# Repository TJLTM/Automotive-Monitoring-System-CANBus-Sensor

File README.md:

What is this? 
--- when working on my AMS solution i kept putting more and more stuff into a single box and everytime i needed to make a change it was $200 for a board that may or may not work so i decided to make it easier on myself to split the sensors up so that it isn't a bespoke solution for a single car application. 

these are the sensor hardware designs that match up with https://github.com/TJLTM/Automotive-Monitoring-System-CANBus-Sensor-FW repo so that i can keep the Hardware designs over here and the FW over there. mostly just so i'm not in some weird state where i'm working on a FW for one thing and the hardware for another and get into a screwed up merge situation. this has happened before in my other projects. 

If you look at the other repo you'll see i've made provisions for the following sensors 
* Temp (RTD)
* Voltage (ADC)
  * Pressure
  * Current
  * Temp (not RTD Based)
  * Any sensor that outputs a votlage signal if gain is needed that would have to be added
* Vacuum
* I/O
* RPM
* LED or other general Output
  * P-channel
  * N-channel  

The other boards ahve the hardware built on to the boards since those require some type of special sensor

Vacuum sensor 
This one is something that i've been working on for a while since there aren't many direct vacuum sensors out there and it took me a while to figure out this design as most vacuum sensors or MAPs so a bit of math to do it. They take the Barometric pressure and then making a few assumptions use the differential to standard atmospherical pressure to give you the vacuum. The design i am using is a direct measurement of the vacuum via the honeywell sensor. Yes it's expensive to build. In fact it costs more to make one of those then all the others combined. 

RPM sensor 
this one is a straight foreward design and i may make it an add on module for the ADC since really it's just a Freq to Voltage Sensor 

The I/O box... 
That one i'm making it a standard 8 in and 8 out setup. can be made to i don't know.... hook into power window units in older cars that can then be remotely controlled or in my case add power windows to some cars.

LED 
General 3 Channel RGB leds can be driven off of this I'm making it 4 channel since i have the space for it. It can either be high or low side switching depending on your application. this is using the 0-255 PWM output of the AVR

I'm using my other design for power https://github.com/TJLTM/LM2670SX-Carrier but if you don't like it. BYOPS

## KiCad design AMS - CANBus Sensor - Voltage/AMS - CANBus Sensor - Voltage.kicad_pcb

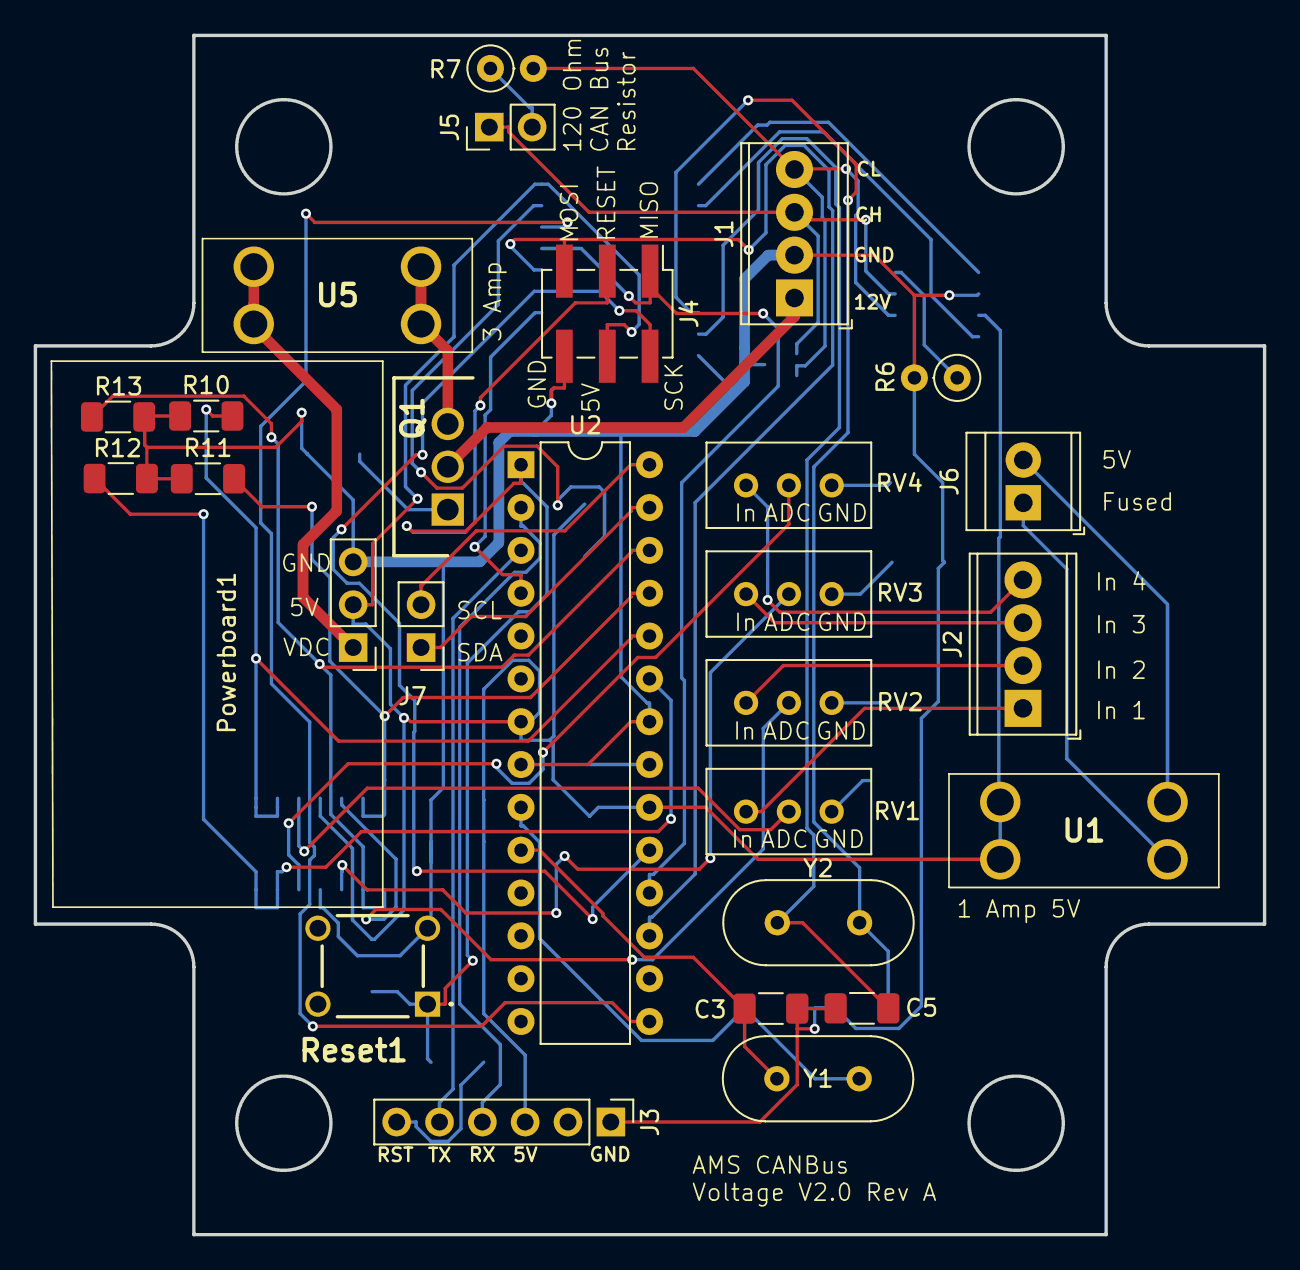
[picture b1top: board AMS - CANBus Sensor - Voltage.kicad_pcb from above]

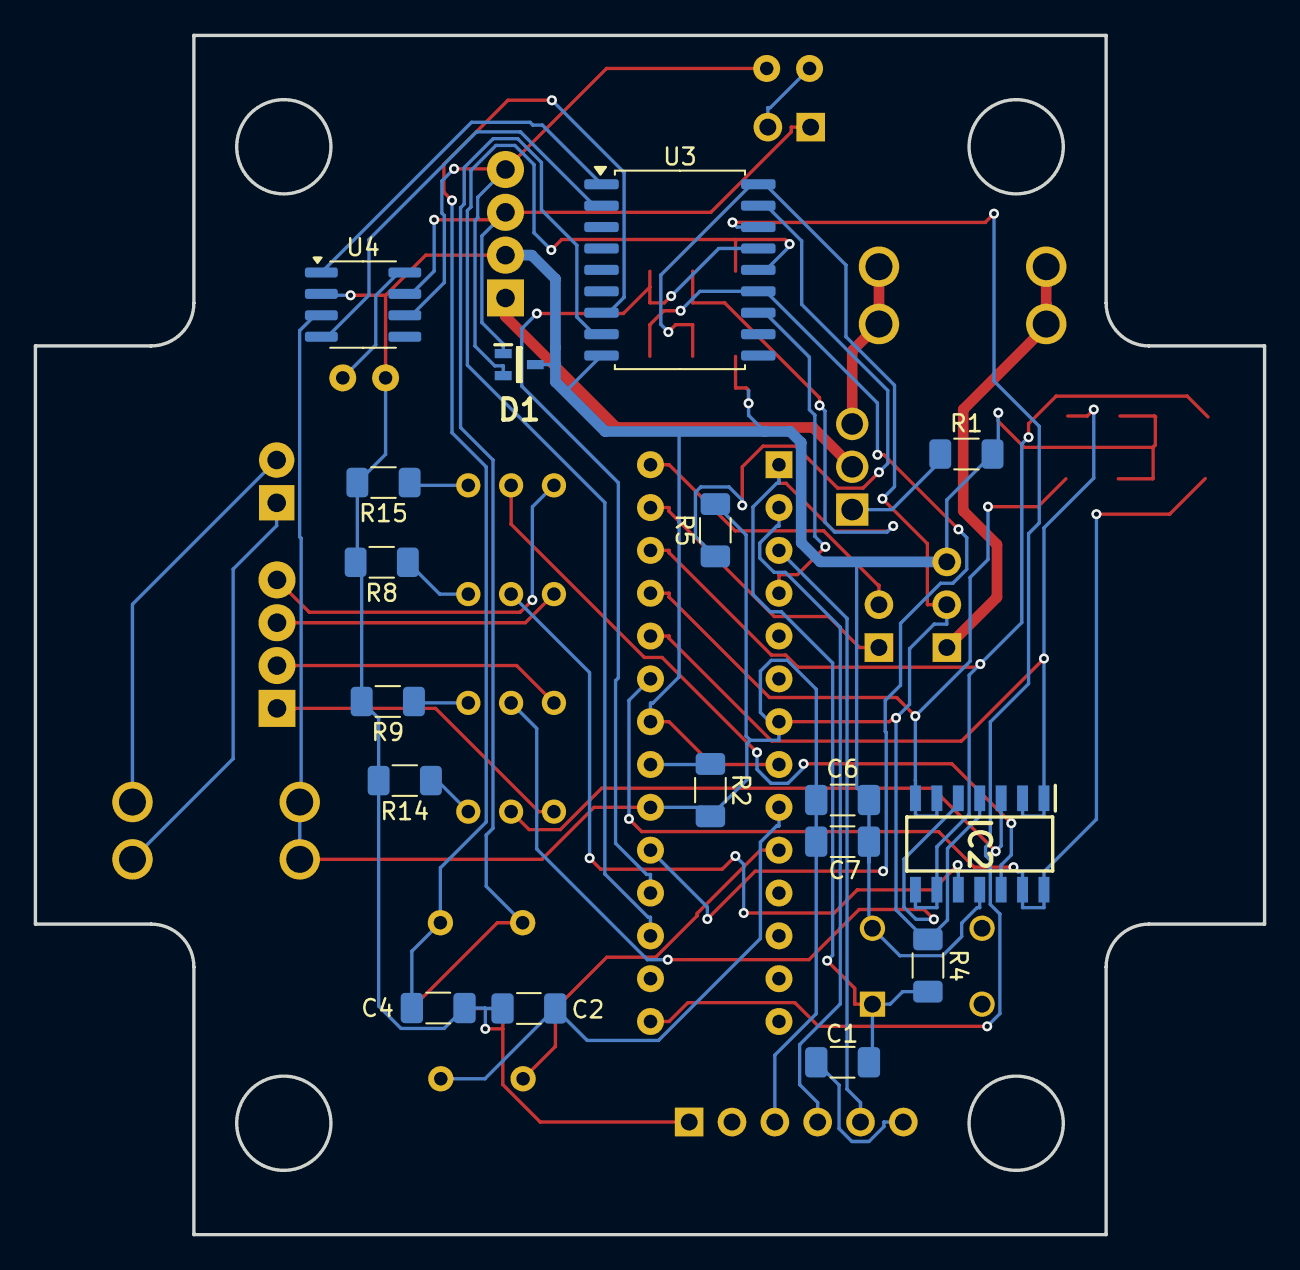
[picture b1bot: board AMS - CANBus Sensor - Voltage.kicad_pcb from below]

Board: 2 copper layers, 72.9 x 71.1 mm, 44 parts (17 on the bottom side), 47 nets.

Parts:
C1, C6, C7: 100nf; C_1206_3216Metric_Pad1.33x1.80mm_HandSolder
C2, C3, C4, C5: 22pf; C_1206_3216Metric_Pad1.33x1.80mm_HandSolder
D1: PESD5V0L2UU,115; SOT65P210X110-3N
IC2: OPA4340UA; SOIC127P600X175-14N
J1, J2: Power_And_CAN; TerminalBlock_Phoenix_MPT-0,5-4-2.54_1x04_P2.54mm_Horizontal
J3: TTL_Programmer; PinHeader_1x06_P2.54mm_Vertical
J4: ICSP; PinHeader_2x03_P2.54mm_Vertical_SMD
J5, J7: Conn_01x02; PinHeader_1x02_P2.54mm_Vertical
J6: Screw_Terminal_01x02; TerminalBlock_TE_282834-2_1x02_P2.54mm_Horizontal
Powerboard1: Conn_01x03; PinHeader_1x03_P2.54mm_Vertical
Q1: IRF9Z34NPBF; TO254P469X1042X1967-3P
R1, R4, R5: 10k; R_1206_3216Metric_Pad1.30x1.75mm_HandSolder
R2: 4.7k; R_1206_3216Metric_Pad1.30x1.75mm_HandSolder
R6: 17k; R_Axial_DIN0207_L6.3mm_D2.5mm_P2.54mm_Vertical
R7: 120; R_Axial_DIN0207_L6.3mm_D2.5mm_P2.54mm_Vertical
R8, R9, R14, R15: 1k; R_1206_3216Metric_Pad1.30x1.75mm_HandSolder
R10, R11, R12, R13: 47K; R_1206_3216Metric_Pad1.30x1.75mm_HandSolder
RV1, RV2, RV3, RV4: 200k; Potentiometer_Bourns_3296W_Vertical
Reset1: TS02-66-160-BK-260-LCR-D; TS0266160BK260LCRD
U1, U5: 3568
U2: ATmega328P-P; DIP-28_W7.62mm
U3: MCP2515-xSO; SOIC-18W_7.5x11.6mm_P1.27mm
U4: MCP2551-I-SN; SOIC-8_3.9x4.9mm_P1.27mm
Y1, Y2: 16MHz; Crystal_HC49-U_Vertical

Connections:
+5V: C6.1, C7.1, IC2.4 (V+), J3.3, J4.4, Powerboard1.2, R2.2, R4.1, R5.2, U1.3, U1.4, U2.7 (VCC), U2.20 (AVCC), U3.18 (VDD), U4.3 (VDD)
+VDC: Powerboard1.1, U5.3, U5.4
/BareMinAtmel328P/AREF: R2.1, U2.21 (AREF)
/BareMinAtmel328P/PB1-D9: U2.15 (PB1), U3.16 (~CS)
/BareMinAtmel328P/PB3-D11-MOSI: J4.5, U2.17 (PB3), U3.14 (SI)
/BareMinAtmel328P/PB4-D12-MISO: J4.1, U2.18 (PB4), U3.15 (SO)
/BareMinAtmel328P/PB5-D13-SCK: J4.2, U2.19 (PB5), U3.13 (SCK)
/BareMinAtmel328P/PC0-A0: IC2.13 (-IN_D), IC2.14 (OUT_D), R12.2, U2.23 (PC0)
/BareMinAtmel328P/PC1-A1: IC2.1 (OUT_A), IC2.2 (-IN_A), R10.2, U2.24 (PC1)
/BareMinAtmel328P/PC2-A2: IC2.6 (-IN_B), IC2.7 (OUT_B), R11.2, U2.25 (PC2)
/BareMinAtmel328P/PC3-A3: IC2.8 (OUT_C), IC2.9 (-IN_C), R13.2, U2.26 (PC3)
/BareMinAtmel328P/PD0-RX: J3.4, U2.2 (PD0)
/BareMinAtmel328P/PD1-TX: J3.5, U2.3 (PD1)
/BareMinAtmel328P/PD2-D2: U2.4 (PD2), U3.12 (~INT)
/BareMinAtmel328P/RESET: C1.2, J4.3, R4.2, Reset1.1 (NO_1), U2.1 (~RESET/PC6)
/BufferedADC/ADCIN1: IC2.3 (+IN_A), RV1.2
/BufferedADC/ADCIN2: IC2.5 (+IN_B), RV2.2
/BufferedADC/ADCIN3: IC2.10 (+IN_C), RV3.2
/BufferedADC/ADCIN4: IC2.12 (+IN_D), RV4.2
/CANBUS-MCP2515/RXtoCANTC: U3.2 (RXCAN), U4.4 (RXD)
/CANBUS-MCP2515/TXtoCANTC: U3.1 (TXCAN), U4.1 (TXD)
CANBUS_H: D1.1 (CATHODE_1), J1.3, J5.1, U4.7 (CANH)
CANBUS_L: D1.2 (CATHODE_2), J1.4, R7.2, U4.6 (CANL)
GND: C2.2, C3.2, C4.2, C5.2, C6.2, C7.2, D1.3 (COMMON_ANODE), IC2.11 (V-), J1.2, J3.1, J4.6, Powerboard1.3, R1.2, R6.2, R8.2, R9.2, R10.1, R11.1, R12.1, R13.1, R14.2, R15.2, Reset1.3 (COM_1), U2.8 (GND), U2.22 (GND), U3.9 (VSS), U4.2 (VSS)
unnamed: J1.1, Q1.2
unnamed: J2.1, RV1.1
unnamed: J2.2, RV2.1
unnamed: J2.3, RV3.1
unnamed: J2.4, RV4.1
unnamed: C1.1, J3.6
unnamed: J5.2, R7.1
unnamed: J6.1, U1.2
unnamed: J6.2, U1.1
unnamed: Q1.1, R1.1
unnamed: Q1.3, U5.1, U5.2
unnamed: R8.1, RV3.3
unnamed: R9.1, RV2.3
unnamed: R14.1, RV1.3
unnamed: R15.1, RV4.3
unnamed: C2.1, U2.9 (XTAL1/PB6), Y1.2
unnamed: C3.1, U2.10 (XTAL2/PB7), Y1.1
unnamed: C5.1, U3.8 (OSC1), Y2.1
unnamed: C4.1, U3.7 (OSC2), Y2.2
unnamed: R5.1, U3.17 (~RESET)
unnamed: R6.1, U4.8 (Rs)
SCL: J7.2, U2.28 (PC5)
SDA: J7.1, U2.27 (PC4)

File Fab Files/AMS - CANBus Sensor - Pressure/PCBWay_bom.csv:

designator,quantity,value,pack,mpn,mount_type
"C1, C6, C7",3,100nf,C_1206_3216Metric_Pad1.33x1.80mm_HandSolder,,smt
"C2, C3, C4, C5",4,22pf,C_1206_3216Metric_Pad1.33x1.80mm_HandSolder,,smt
D1,1,"PESD5V0L2UU,115",SOT65P210X110-3N,,smt
IC2,1,OPA4340UA,SOIC127P600X175-14N,,smt
"J1, J2",2,Power_And_CAN,"TerminalBlock_Phoenix_MPT-0,5-4-2.54_1x04_P2.54mm_Horizontal",,tht
J3,1,TTL_Programmer,PinHeader_1x06_P2.54mm_Vertical,,tht
J4,1,ICSP,PinHeader_2x03_P2.54mm_Vertical_SMD,,smt
J5,1,Conn_01x02,PinHeader_1x02_P2.54mm_Vertical,,tht
J6,1,Screw_Terminal_01x02,"TerminalBlock_Phoenix_MPT-0,5-2-2.54_1x02_P2.54mm_Horizontal",,tht
NTC1,1,10k,R_Axial_DIN0207_L6.3mm_D2.5mm_P2.54mm_Vertical,,tht
Powerboard1,1,Conn_01x03,PinHeader_1x03_P2.54mm_Vertical,,tht
Q1,1,IRF9Z34NPBF,TO254P469X1042X1967-3P,,tht
"R1, R3, R4, R5",4,10k,R_1206_3216Metric_Pad1.30x1.75mm_HandSolder,,smt
"R10, R11, R12, R13",4,47K,R_1206_3216Metric_Pad1.30x1.75mm_HandSolder,,smt
"R14, R15, R8, R9",4,100K,R_1206_3216Metric_Pad1.30x1.75mm_HandSolder,,smt
R2,1,4.7k,R_1206_3216Metric_Pad1.30x1.75mm_HandSolder,,smt
R6,1,17k,R_Axial_DIN0207_L6.3mm_D2.5mm_P2.54mm_Vertical,,tht
R7,1,120,R_Axial_DIN0207_L6.3mm_D2.5mm_P2.54mm_Vertical,,tht
"RV1, RV2, RV3, RV4",4,200k,Potentiometer_Bourns_3296W_Vertical,,tht
Reset1,1,TS02-66-160-BK-260-LCR-D,TS0266160BK260LCRD,,tht
"U1, U5",2,3568,3568,,tht
U2,1,ATmega328P-P,DIP-28_W7.62mm,,tht
U3,1,MCP2515-xSO,SOIC-18W_7.5x11.6mm_P1.27mm,,smt
U4,1,MCP2551-I-SN,SOIC-8_3.9x4.9mm_P1.27mm,,smt
"Y1, Y2",2,16MHz,Crystal_HC49-U_Vertical,,tht

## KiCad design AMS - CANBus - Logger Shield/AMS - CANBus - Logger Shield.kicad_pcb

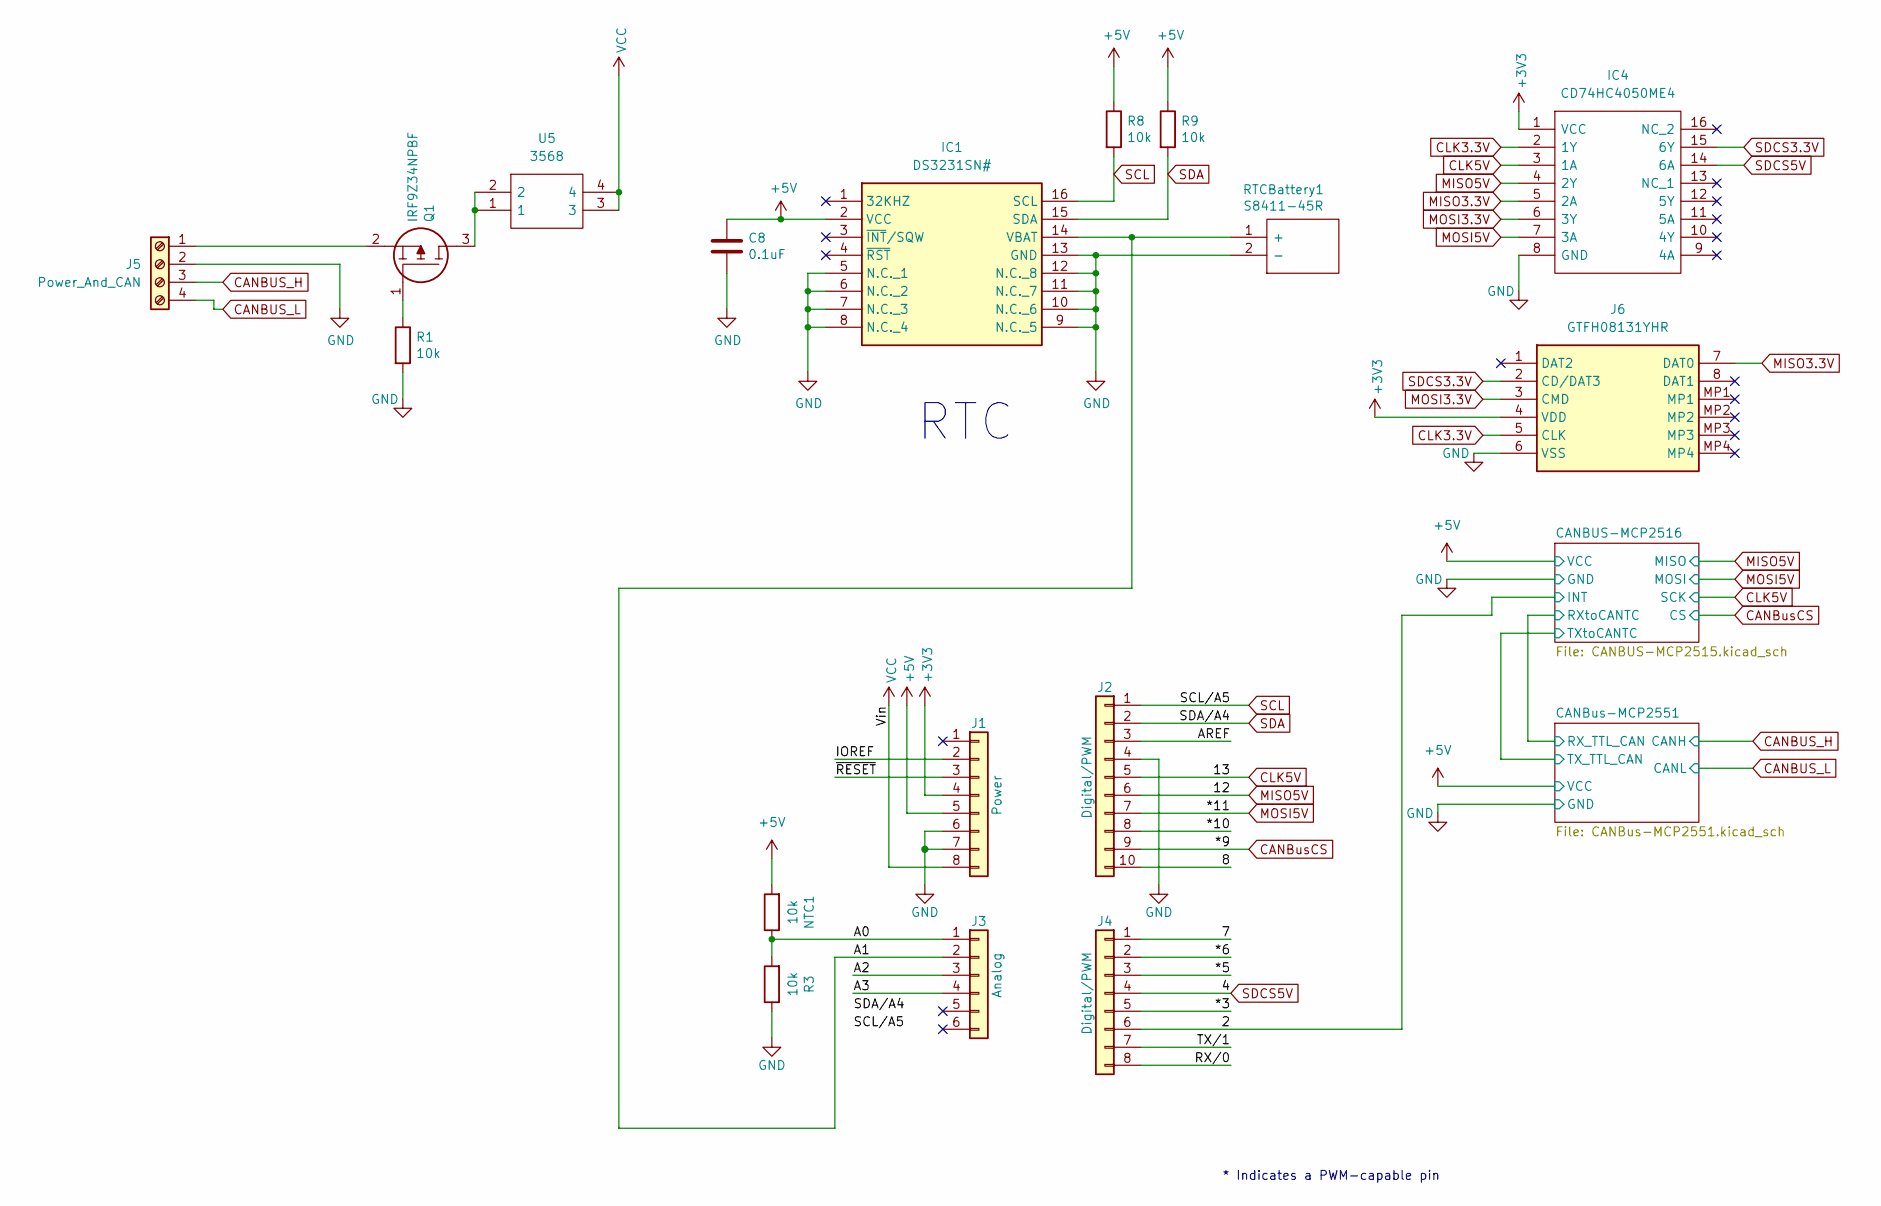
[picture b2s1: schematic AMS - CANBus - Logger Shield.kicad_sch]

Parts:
C8: 0.1uF; C_1206_3216Metric_Pad1.33x1.80mm_HandSolder
IC1: DS3231SN#; SOIC127P1032X265-16N; Mouser Part Number 700-DS3231SN#
IC4: CD74HC4050ME4; SOIC127P600X175-16N; Mouser Part Number 595-CD74HC4050ME4
J1: Power; PinSocket_1x08_P2.54mm_Vertical
J2: Digital/PWM; PinSocket_1x10_P2.54mm_Vertical
J3: Analog; PinSocket_1x06_P2.54mm_Vertical
J4: Digital/PWM; PinSocket_1x08_P2.54mm_Vertical
J5: Power_And_CAN; TerminalBlock_Phoenix_MPT-0,5-4-2.54_1x04_P2.54mm_Horizontal
J6: GTFH08131YHR; Mouser Part Number 523-GTFH08131YHR
NTC1: 10k; R_Axial_DIN0207_L6.3mm_D2.5mm_P2.54mm_Vertical
Q1: IRF9Z34NPBF; TO254P469X1042X1967-3P; Mouser Part Number 942-IRF9Z34NPBF
R1, R3, R8, R9: 10k; R_1206_3216Metric_Pad1.30x1.75mm_HandSolder
RTCBattery1: S8411-45R; S8411-45R_1; Mouser Part Number 855-S8411-45R
U5: 3568; Mouser Part Number 534-3568

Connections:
+3V3: IC4.1 (VCC), J1.4, J6.4 (VDD)
+5V: C8.1, IC1.2 (VCC), J1.5, NTC1.2, R8.1, R9.1; also elsewhere on the board
/2: J4.6; also elsewhere on the board
/7: J4.1
/8: J2.10
/*3: J4.5
/*5: J4.3
/*6: J4.2
/*10: J2.8
/A0: J3.1, NTC1.1, R3.2
/A1: IC1.14 (VBAT), J3.2, RTCBattery1.1 (+)
/A2: J3.3
/A3: J3.4
/AREF: J2.3
/IOREF: J1.2
/RX/0: J4.8
/TX/1: J4.7
/~RESET: J1.3
CANBUS_H: J5.3; also elsewhere on the board
CANBUS_L: J5.4; also elsewhere on the board
CANBusCS: J2.9; also elsewhere on the board
CLK3.3V: IC4.2 (1Y), J6.5 (CLK)
CLK5V: IC4.3 (1A), J2.5; also elsewhere on the board
GND: C8.2, IC1.5 (N.C._1), IC1.6 (N.C._2), IC1.7 (N.C._3), IC1.8 (N.C._4), IC1.9 (N.C._5), IC1.10 (N.C._6), IC1.11 (N.C._7), IC1.12 (N.C._8), IC1.13 (GND), IC4.8 (GND), J1.6, J1.7, J2.4, J5.2, J6.6 (VSS), R1.2, R3.1, RTCBattery1.2 (-); also elsewhere on the board
MISO3.3V: IC4.5 (2A), J6.7 (DAT0)
MISO5V: IC4.4 (2Y), J2.6; also elsewhere on the board
MOSI3.3V: IC4.6 (3Y), J6.3 (CMD)
MOSI5V: IC4.7 (3A), J2.7; also elsewhere on the board
unnamed: J5.1, Q1.2
unnamed: Q1.1, R1.1
unnamed: Q1.3, U5.1, U5.2
SCL: IC1.16 (SCL), J2.1, R8.2
SDA: IC1.15 (SDA), J2.2, R9.2
SDCS3.3V: IC4.15 (6Y), J6.2 (CD/DAT3)
SDCS5V: IC4.14 (6A), J4.4
VCC: J1.8, U5.3, U5.4

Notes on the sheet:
RTC
* Indicates a PWM-capable pin

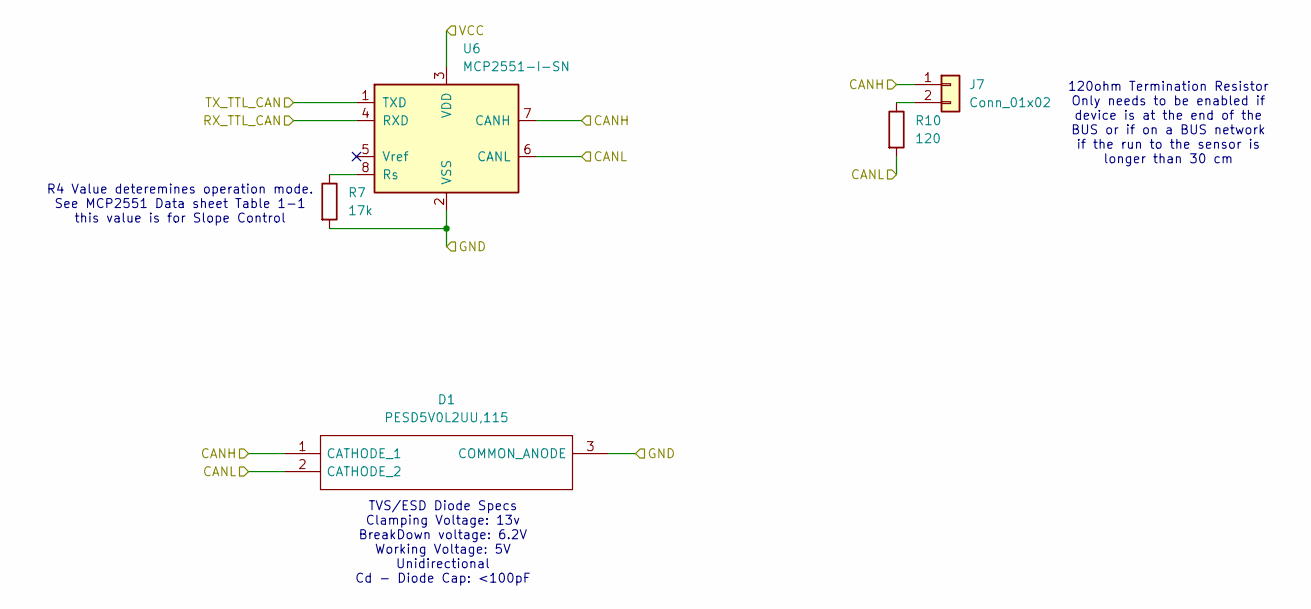
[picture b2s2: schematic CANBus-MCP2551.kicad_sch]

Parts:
D1: PESD5V0L2UU,115; SOT65P210X110-3N; Mouser Part Number 771-PESD5V0L2UU115
J7: Conn_01x02; PinHeader_1x02_P2.54mm_Vertical
R7: 17k; R_Axial_DIN0207_L6.3mm_D2.5mm_P2.54mm_Vertical
R10: 120; R_Axial_DIN0207_L6.3mm_D2.5mm_P2.54mm_Vertical
U6: MCP2551-I-SN; SOIC-8_3.9x4.9mm_P1.27mm

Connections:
+5V: U6.3 (VDD); also elsewhere on the board
/CANBUS-MCP2516/RXtoCANTC: U6.4 (RXD); also elsewhere on the board
/CANBUS-MCP2516/TXtoCANTC: U6.1 (TXD); also elsewhere on the board
CANBUS_H: D1.1 (CATHODE_1), J7.1, U6.7 (CANH); also elsewhere on the board
CANBUS_L: D1.2 (CATHODE_2), R10.2, U6.6 (CANL); also elsewhere on the board
GND: D1.3 (COMMON_ANODE), R7.2, U6.2 (VSS); also elsewhere on the board
unnamed: J7.2, R10.1
unnamed: R7.1, U6.8 (Rs)

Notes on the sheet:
R4 Value deteremines operation mode. See MCP2551 Data sheet Table 1-1 this value is for Slope Control
120ohm Termination Resistor Only needs to be enabled if device is at the end of the BUS or if on a BUS network if the run to the sensor is longer than 30 cm
TVS/ESD Diode Specs Clamping Voltage: 13v BreakDown voltage: 6.2V Working Voltage: 5V Unidirectional Cd - Diode Cap: <100pF

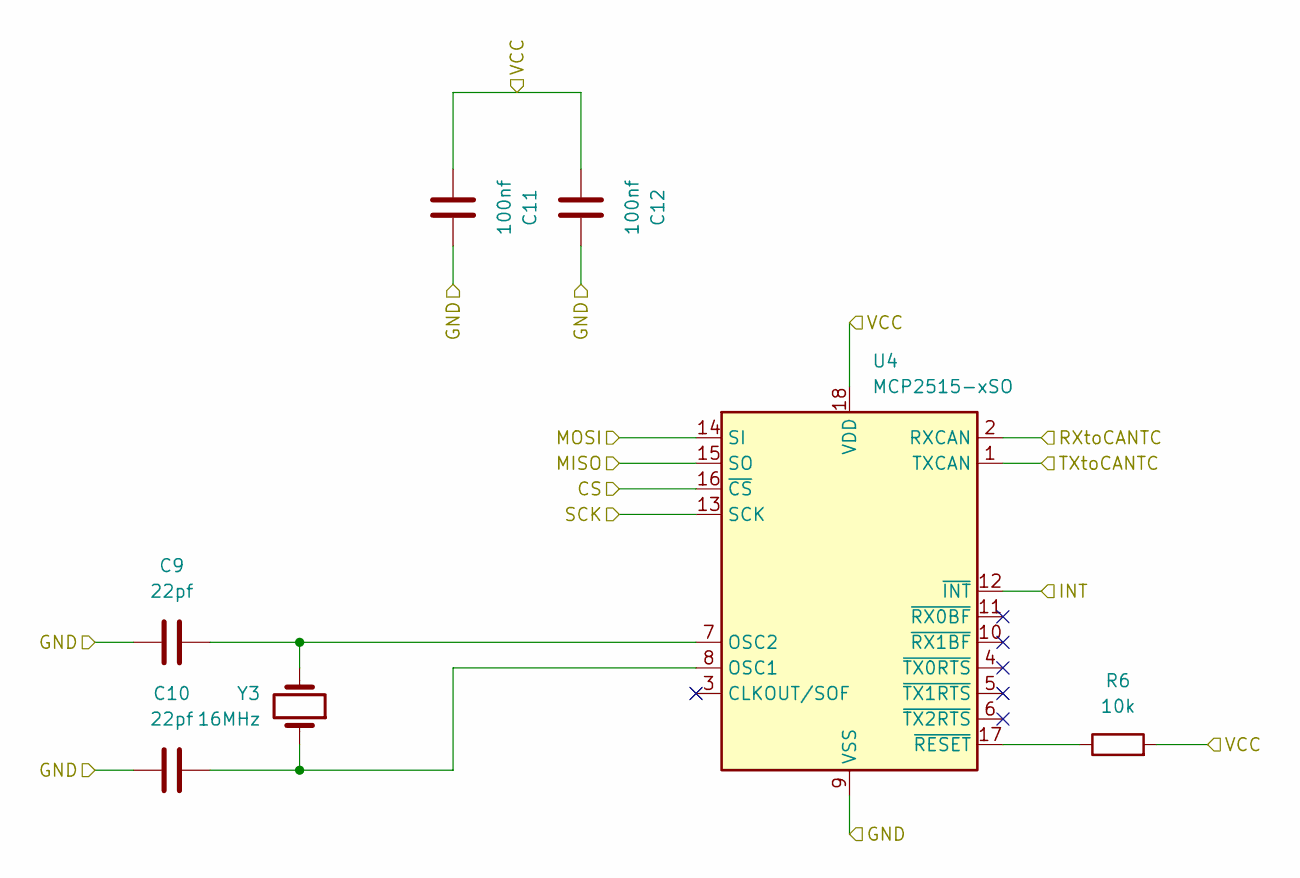
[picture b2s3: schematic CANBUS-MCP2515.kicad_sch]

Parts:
C9, C10: 22pf; C_1206_3216Metric_Pad1.33x1.80mm_HandSolder
C11, C12: 100nf; C_1206_3216Metric_Pad1.33x1.80mm_HandSolder
R6: 10k; R_1206_3216Metric_Pad1.30x1.75mm_HandSolder
U4: MCP2515-xSO; SOIC-18W_7.5x11.6mm_P1.27mm
Y3: 16MHz; Crystal_HC49-U_Vertical

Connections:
+5V: C11.1, C12.1, R6.2, U4.18 (VDD); also elsewhere on the board
/2: U4.12 (~INT); also elsewhere on the board
/CANBUS-MCP2516/RXtoCANTC: U4.2 (RXCAN); also elsewhere on the board
/CANBUS-MCP2516/TXtoCANTC: U4.1 (TXCAN); also elsewhere on the board
CANBusCS: U4.16 (~CS); also elsewhere on the board
CLK5V: U4.13 (SCK); also elsewhere on the board
GND: C9.2, C10.2, C11.2, C12.2, U4.9 (VSS); also elsewhere on the board
MISO5V: U4.15 (SO); also elsewhere on the board
MOSI5V: U4.14 (SI); also elsewhere on the board
unnamed: C10.1, U4.8 (OSC1), Y3.1
unnamed: C9.1, U4.7 (OSC2), Y3.2
unnamed: R6.1, U4.17 (~RESET)

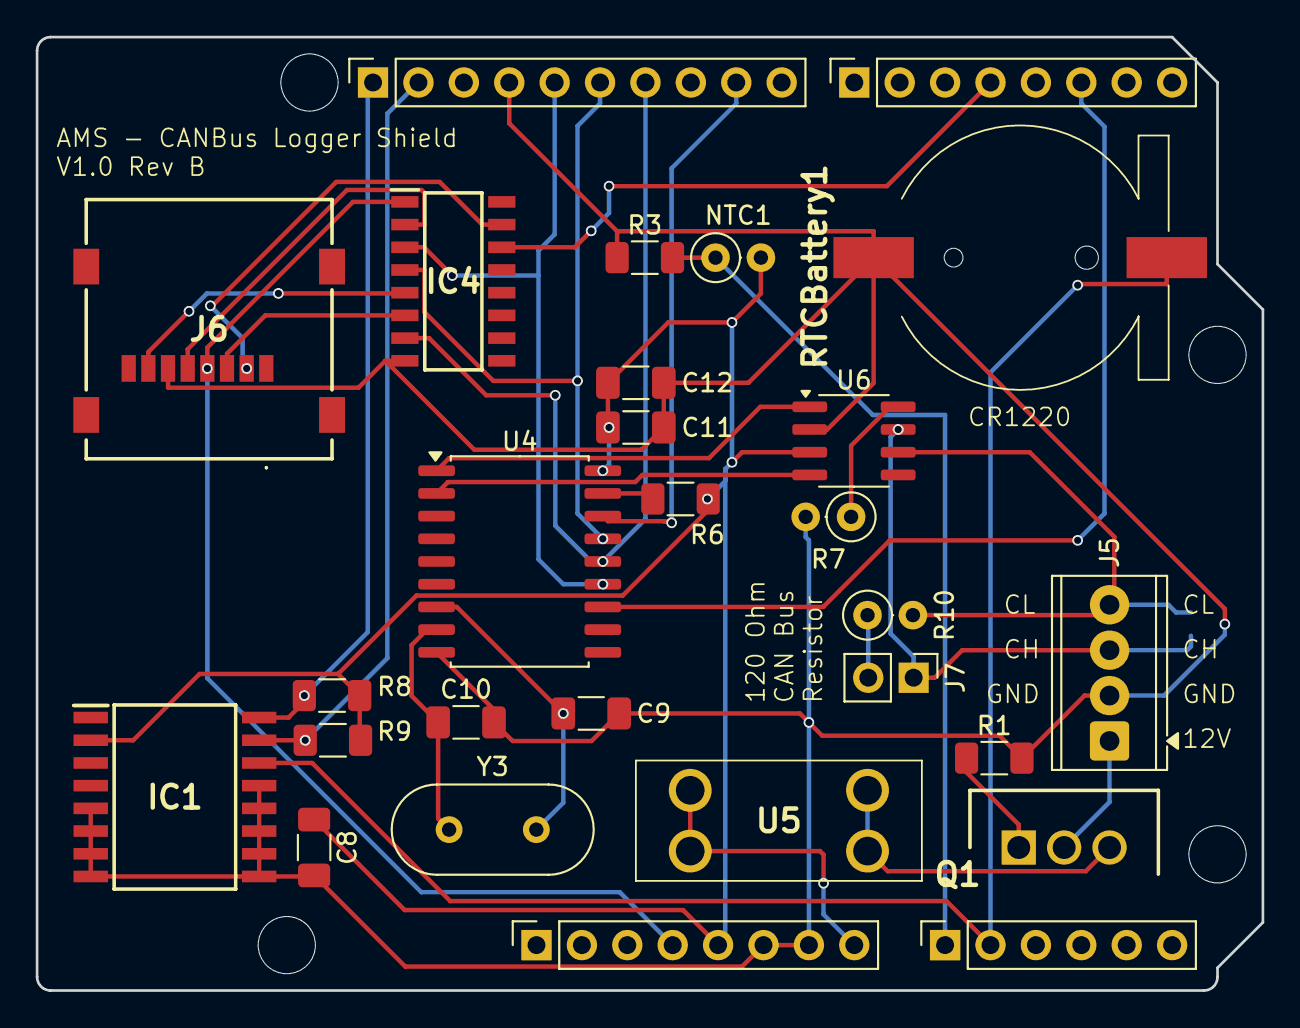
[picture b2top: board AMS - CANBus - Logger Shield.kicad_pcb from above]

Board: 2 copper layers, 68.6 x 53.3 mm, 33 parts (1 on the bottom side), 30 nets.

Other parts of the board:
MH1, MH2, MH3, MH4: MountingHole_3.2mm

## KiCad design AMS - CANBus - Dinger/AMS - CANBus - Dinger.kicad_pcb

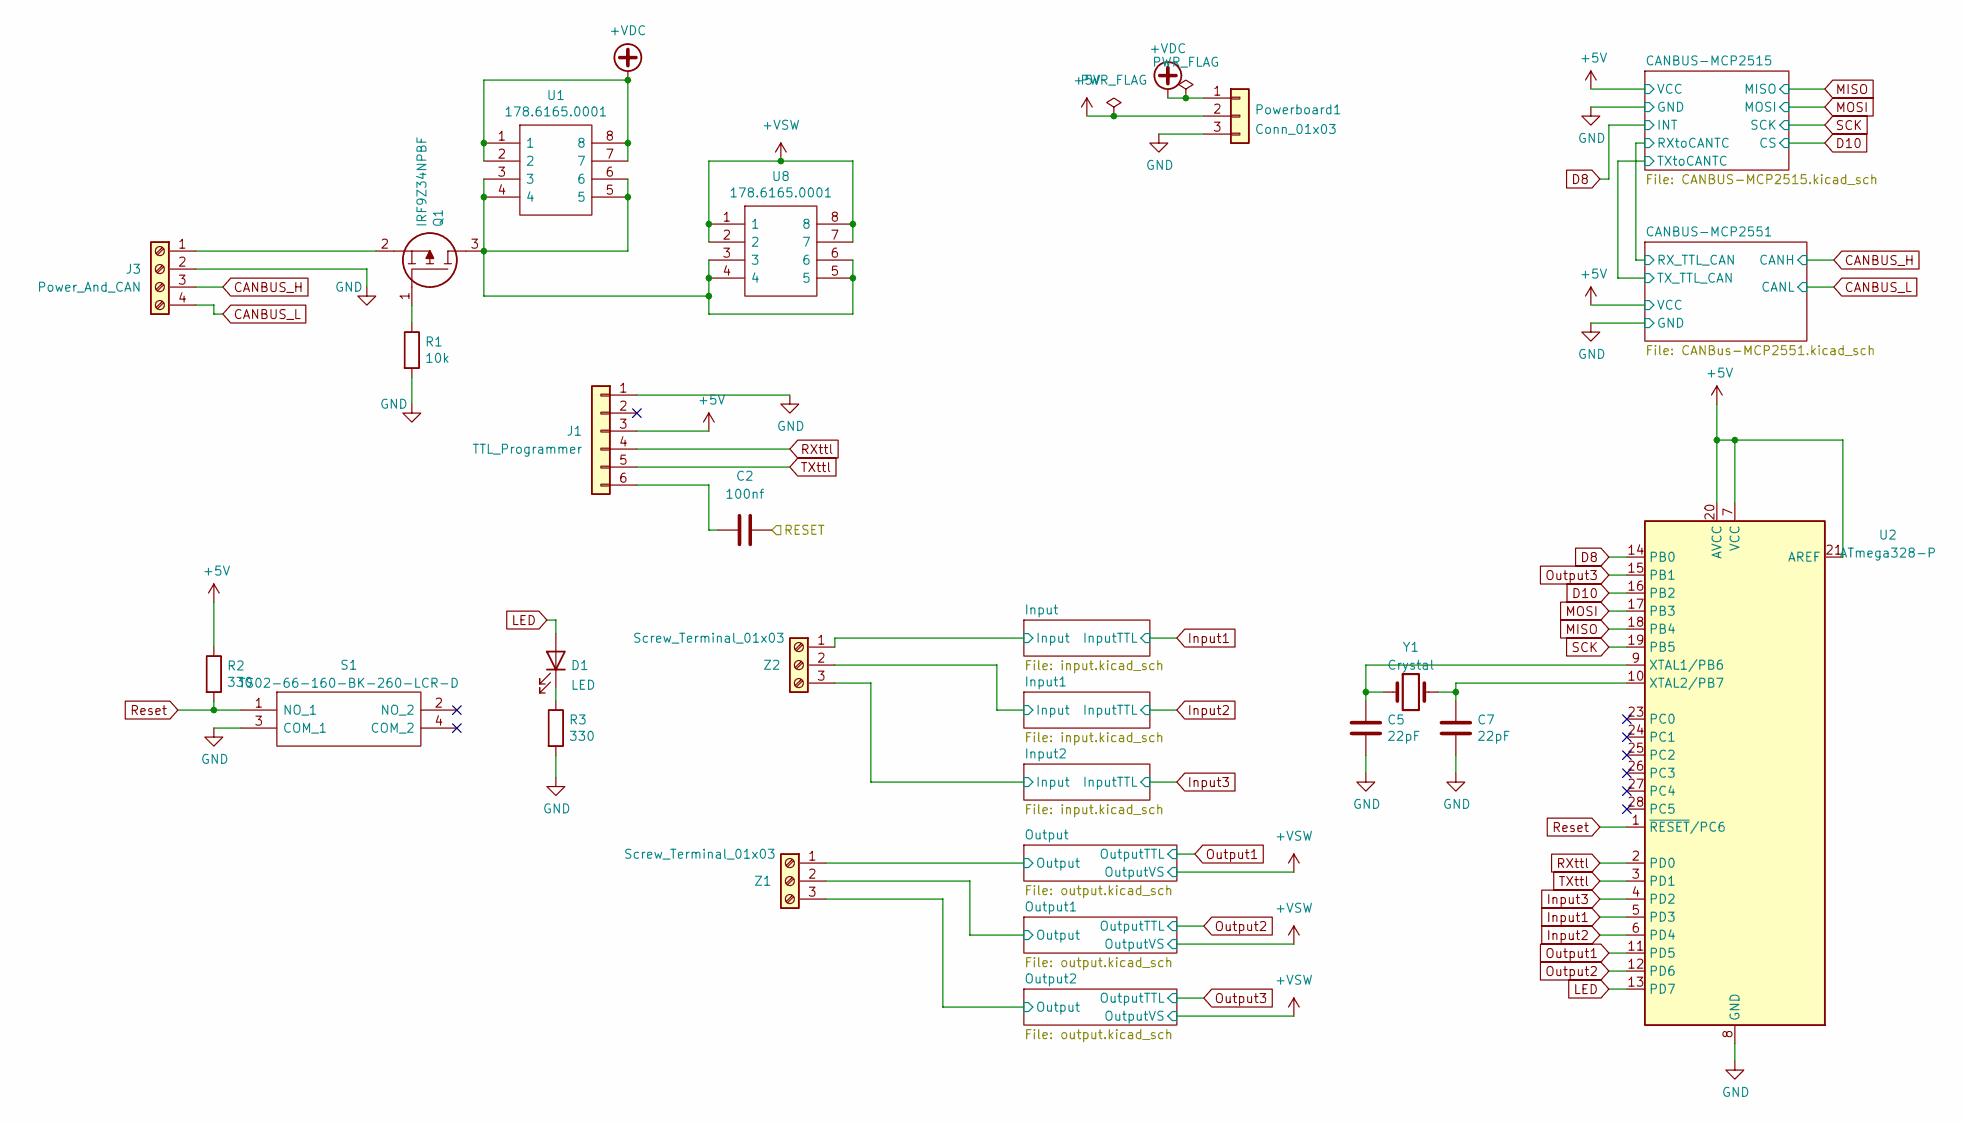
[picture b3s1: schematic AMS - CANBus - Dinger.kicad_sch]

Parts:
C2: 100nf; C_1206_3216Metric_Pad1.33x1.80mm_HandSolder
C5, C7: 22pF; C_1206_3216Metric_Pad1.33x1.80mm_HandSolder
D1: LED; LED_D3.0mm
J1: TTL_Programmer; PinHeader_1x06_P2.54mm_Vertical
J3: Power_And_CAN; TerminalBlock_Phoenix_MPT-0,5-4-2.54_1x04_P2.54mm_Horizontal
Powerboard1: Conn_01x03; PinHeader_1x03_P2.54mm_Vertical
Q1: IRF9Z34NPBF; TO254P469X1042X1967-3P; Mouser Part Number 942-IRF9Z34NPBF
R1: 10k; R_1206_3216Metric_Pad1.30x1.75mm_HandSolder
R2, R3: 330; R_1206_3216Metric_Pad1.30x1.75mm_HandSolder
S1: TS02-66-160-BK-260-LCR-D; TS0266160BK260LCRD; Mouser Part Number 179-TS0266160BK260LC
U1, U8: 178.6165.0001; 17861650001; Mouser Part Number 576-178.6165.0001
U2: ATmega328-P; DIP-28_W7.62mm
Y1: Crystal; Crystal_HC49-U_Vertical
Z1, Z2: Screw_Terminal_01x03; TerminalBlock_Phoenix_MKDS-1,5-3-5.08_1x03_P5.08mm_Horizont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

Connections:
+5V: J1.3, Powerboard1.2, R2.1, U2.7 (VCC), U2.20 (AVCC), U2.21 (AREF); also elsewhere on the board
+VDC: Powerboard1.1, U1.1, U1.2, U1.7, U1.8
+VSW: U8.1, U8.2, U8.7, U8.8; also elsewhere on the board
/Input1/Input: Z2.2; also elsewhere on the board
/Input2/Input: Z2.3; also elsewhere on the board
/Input/Input: Z2.1; also elsewhere on the board
/Output1/Output: Z1.2; also elsewhere on the board
/Output2/Output: Z1.3; also elsewhere on the board
/Output/Output: Z1.1; also elsewhere on the board
/RESET: C2.2
CANBUS_H: J3.3; also elsewhere on the board
CANBUS_L: J3.4; also elsewhere on the board
D8: U2.14 (PB0); also elsewhere on the board
D10: U2.16 (PB2); also elsewhere on the board
GND: C5.2, C7.2, J1.1, J3.2, Powerboard1.3, R1.2, R3.2, S1.3 (COM_1), U2.8 (GND), U2.22 (GND); also elsewhere on the board
Input1: U2.5 (PD3); also elsewhere on the board
Input2: U2.6 (PD4); also elsewhere on the board
Input3: U2.4 (PD2); also elsewhere on the board
LED: D1.2 (A), U2.13 (PD7)
MISO: U2.18 (PB4); also elsewhere on the board
MOSI: U2.17 (PB3); also elsewhere on the board
unnamed: D1.1 (K), R3.1
unnamed: C2.1, J1.6
unnamed: J3.1, Q1.2
unnamed: Q1.1, R1.1
unnamed: Q1.3, U1.3, U1.4, U1.5, U1.6, U8.3, U8.4, U8.5, U8.6
unnamed: C5.1, U2.9 (XTAL1/PB6), Y1.1
unnamed: C7.1, U2.10 (XTAL2/PB7), Y1.2
Output1: U2.11 (PD5); also elsewhere on the board
Output2: U2.12 (PD6); also elsewhere on the board
Output3: U2.15 (PB1); also elsewhere on the board
RXttl: J1.4, U2.2 (PD0)
Reset: R2.2, S1.1 (NO_1), U2.1 (~RESET/PC6)
SCK: U2.19 (PB5); also elsewhere on the board
TXttl: J1.5, U2.3 (PD1)

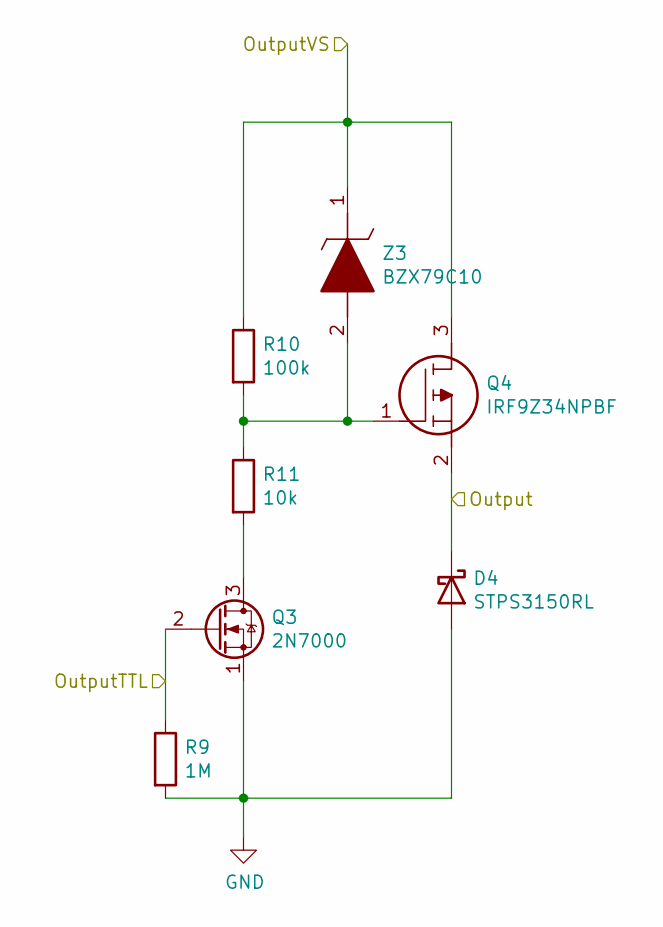
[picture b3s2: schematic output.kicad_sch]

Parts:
D4: STPS3150RL; D_DO-201_P15.24mm_Horizontal
Q3: 2N7000; TO-92_Inline
Q4: IRF9Z34NPBF; TO254P469X1042X1967-3P; Mouser Part Number 942-IRF9Z34NPBF
R9: 1M; R_1206_3216Metric_Pad1.30x1.75mm_HandSolder
R10: 100k; R_1206_3216Metric_Pad1.30x1.75mm_HandSolder
R11: 10k; R_1206_3216Metric_Pad1.30x1.75mm_HandSolder
Z3: BZX79C10; DIOAD1068W53L380D172; Mouser Part Number 512-BZX79C10

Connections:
+VSW: Q4.3, R10.1, Z3.1; also elsewhere on the board
/Output/Output: D4.1 (K), Q4.2; also elsewhere on the board
GND: D4.2 (A), Q3.1 (S), R9.2; also elsewhere on the board
unnamed: Q3.3 (D), R11.2
unnamed: Q4.1, R10.2, R11.1, Z3.2
Output1: Q3.2 (G), R9.1; also elsewhere on the board

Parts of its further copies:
D7, D8: STPS3150RL; D_DO-201_P15.24mm_Horizontal
Q5, Q7: 2N7000; TO-92_Inline
Q8, Q10: IRF9Z34NPBF; TO254P469X1042X1967-3P; Mouser Part Number 942-IRF9Z34NPBF
R21, R24: 100k; R_1206_3216Metric_Pad1.30x1.75mm_HandSolder
R22, R25: 10k; R_1206_3216Metric_Pad1.30x1.75mm_HandSolder
R23: 1M; R_1206_3216Metric_Pad1.30x1.75mm_HandSolder
Z4, Z5: BZX79C10; DIOAD1068W53L380D172; Mouser Part Number 512-BZX79C10

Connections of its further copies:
+VSW: Q8.3, Q10.3, R21.1, R24.1, Z4.1, Z5.1; also elsewhere on the board
/Output1/Output: D7.1 (K), Q8.2; also elsewhere on the board
/Output2/Output: D8.1 (K), Q10.2; also elsewhere on the board
GND: D7.2 (A), D8.2 (A), Q5.1 (S), Q7.1 (S), R23.2; also elsewhere on the board
unnamed 25: Q5.2 (G); also elsewhere on the board
unnamed 35: Q5.3 (D); also elsewhere on the board
unnamed: Q7.3 (D), R22.2
unnamed: Q8.1, R21.2, R22.1, Z4.2
unnamed 39: R25.2; also elsewhere on the board
unnamed: Q10.1, R24.2, R25.1, Z5.2
Output2: Q7.2 (G); also elsewhere on the board
Output3: R23.1; also elsewhere on the board

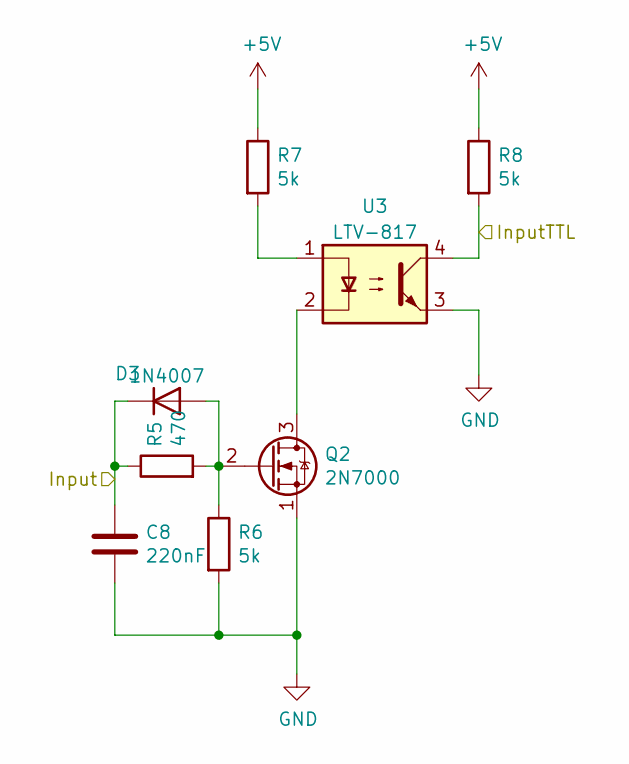
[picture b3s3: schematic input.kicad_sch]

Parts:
C8: 220nF; C_1206_3216Metric_Pad1.33x1.80mm_HandSolder
D3: 1N4007; D_DO-41_SOD81_P10.16mm_Horizontal
Q2: 2N7000; TO-92_Inline
R5: 470; R_1206_3216Metric_Pad1.30x1.75mm_HandSolder
R6, R7, R8: 5k; R_1206_3216Metric_Pad1.30x1.75mm_HandSolder
U3: LTV-817; DIP-4_W7.62mm

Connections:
+5V: R7.1, R8.1; also elsewhere on the board
/Input/Input: C8.1, D3.1 (K), R5.1; also elsewhere on the board
GND: C8.2, Q2.1 (S), R6.2, U3.3; also elsewhere on the board
Input1: R8.2, U3.4; also elsewhere on the board
unnamed: D3.2 (A), Q2.2 (G), R5.2, R6.1
unnamed: Q2.3 (D), U3.2
unnamed: R7.2, U3.1

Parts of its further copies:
C9, C10: 220nF; C_1206_3216Metric_Pad1.33x1.80mm_HandSolder
D5, D6: 1N4007; D_DO-41_SOD81_P10.16mm_Horizontal
Q5, Q6, Q7: 2N7000; TO-92_Inline
R12, R16: 470; R_1206_3216Metric_Pad1.30x1.75mm_HandSolder
R13, R14, R15, R17, R18, R19: 5k; R_1206_3216Metric_Pad1.30x1.75mm_HandSolder
U4, U5: LTV-817; DIP-4_W7.62mm

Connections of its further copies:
+5V: R14.1, R15.1, R18.1, R19.1; also elsewhere on the board
/Input1/Input: C9.1, D5.1 (K), R12.1; also elsewhere on the board
/Input2/Input: C10.1, D6.1 (K), R16.1; also elsewhere on the board
GND: C9.2, C10.2, Q5.1 (S), Q6.1 (S), Q7.1 (S), R13.2, R17.2, U4.3, U5.3; also elsewhere on the board
Input2: R15.2, U4.4; also elsewhere on the board
Input3: R19.2, U5.4; also elsewhere on the board
unnamed: D5.2 (A), Q5.2 (G), R12.2, R13.1
unnamed: D6.2 (A), Q6.2 (G), R16.2, R17.1
unnamed: Q5.3 (D), U4.2
unnamed: Q6.3 (D), U5.2
unnamed 37: Q7.3 (D); also elsewhere on the board
unnamed: R14.2, U4.1
unnamed: R18.2, U5.1
Output2: Q7.2 (G); also elsewhere on the board
